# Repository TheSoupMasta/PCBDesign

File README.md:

In the branches section are all the different projects that these PCBs belong to. Check them out!

This branch features some general use PCBs for many different applications.
General Use:
- MUXBreakout v2.sch and MUXBreakout v6.brd. Made for attaching to the RCJ baseplate. May not be in a desirable shape, so be wary. Otherwise, very useful to have around if you run out of analog pins on your PCB.

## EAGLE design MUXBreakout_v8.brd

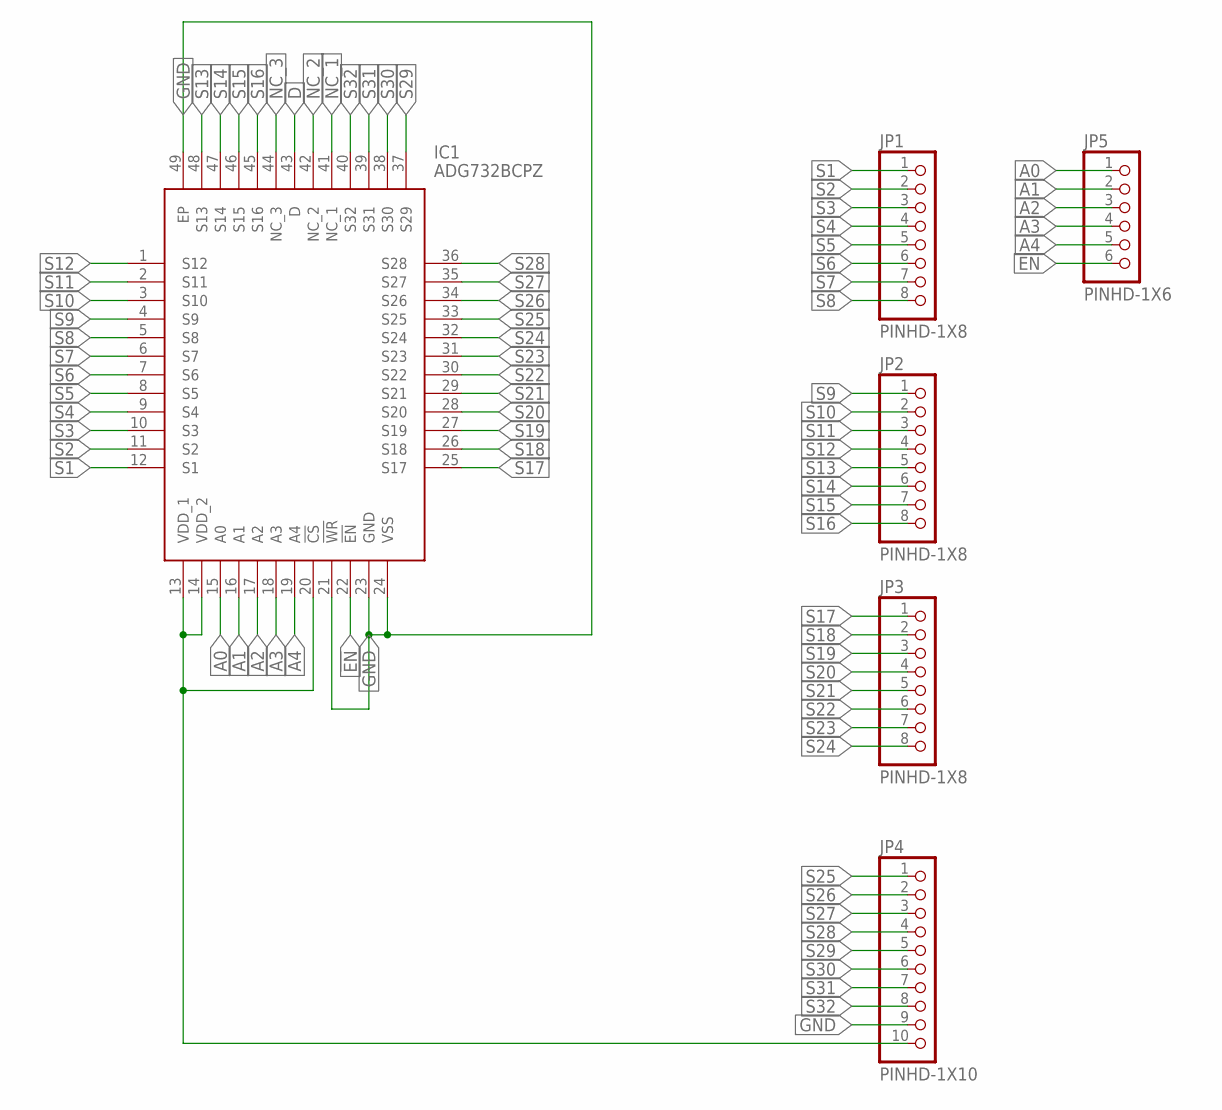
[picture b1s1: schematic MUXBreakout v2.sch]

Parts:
IC1: ADG732BCPZ; QFN50P700X700X100-49N
JP1, JP2, JP3: PINHD-1X8; 1X08
JP4: PINHD-1X10; 1X10
JP5: PINHD-1X6; 1X06

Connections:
!EN: IC1.22 (!EN), JP5.6
A0: IC1.15 (A0), JP5.1
A1: IC1.16 (A1), JP5.2
A2: IC1.17 (A2), JP5.3
A3: IC1.18 (A3), JP5.4
A4: IC1.19 (A4), JP5.5
D: IC1.43 (D)
GND: IC1.21 (!WR), IC1.23 (GND), IC1.24 (VSS), IC1.49 (EP), JP4.9
NC_1: IC1.41 (NC_1)
NC_2: IC1.42 (NC_2)
NC_3: IC1.44 (NC_3)
S1: IC1.12 (S1), JP1.1
S2: IC1.11 (S2), JP1.2
S3: IC1.10 (S3), JP1.3
S4: IC1.9 (S4), JP1.4
S5: IC1.8 (S5), JP1.5
S6: IC1.7 (S6), JP1.6
S7: IC1.6 (S7), JP1.7
S8: IC1.5 (S8), JP1.8
S9: IC1.4 (S9), JP2.1
S10: IC1.3 (S10), JP2.2
S11: IC1.2 (S11), JP2.3
S12: IC1.1 (S12), JP2.4
S13: IC1.48 (S13), JP2.5
S14: IC1.47 (S14), JP2.6
S15: IC1.46 (S15), JP2.7
S16: IC1.45 (S16), JP2.8
S17: IC1.25 (S17), JP3.1
S18: IC1.26 (S18), JP3.2
S19: IC1.27 (S19), JP3.3
S20: IC1.28 (S20), JP3.4
S21: IC1.29 (S21), JP3.5
S22: IC1.30 (S22), JP3.6
S23: IC1.31 (S23), JP3.7
S24: IC1.32 (S24), JP3.8
S25: IC1.33 (S25), JP4.1
S26: IC1.34 (S26), JP4.2
S27: IC1.35 (S27), JP4.3
S28: IC1.36 (S28), JP4.4
S29: IC1.37 (S29), JP4.5
S30: IC1.38 (S30), JP4.6
S31: IC1.39 (S31), JP4.7
S32: IC1.40 (S32), JP4.8
VDD_2: IC1.13 (VDD_1), IC1.14 (VDD_2), IC1.20 (!CS), JP4.10

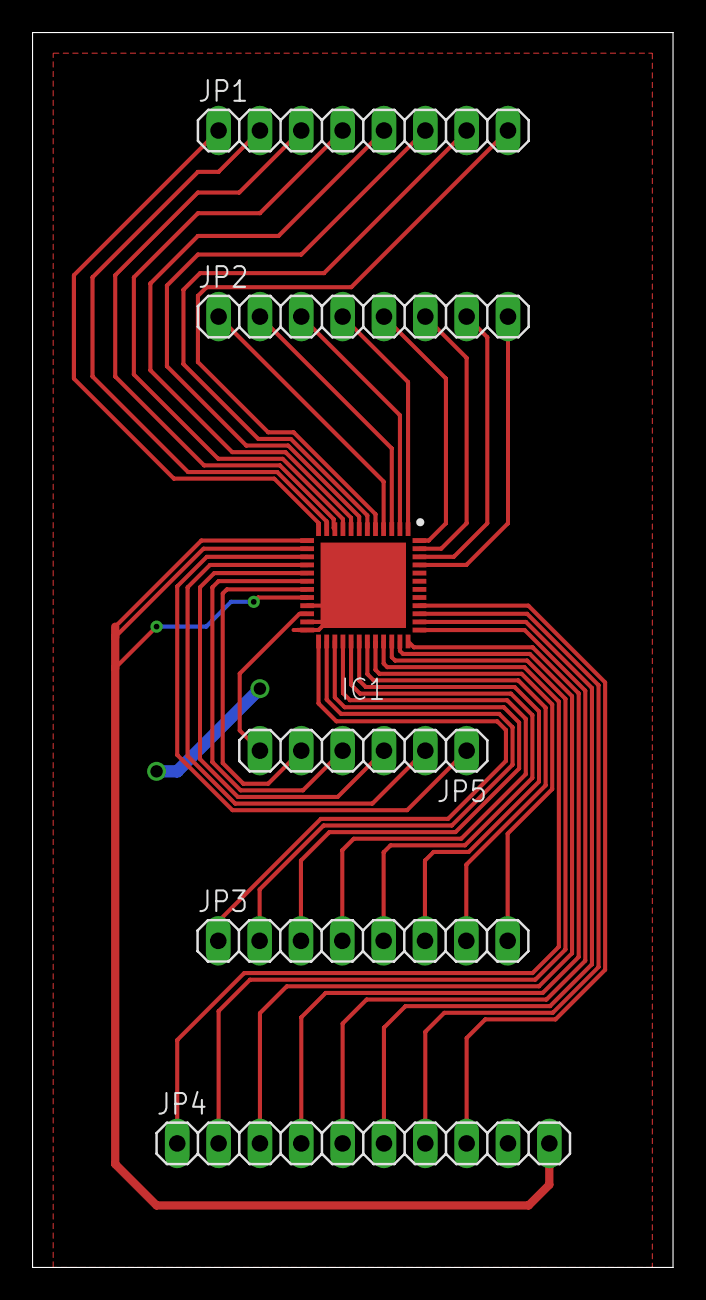
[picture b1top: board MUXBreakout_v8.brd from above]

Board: 2 copper layers, 39.4 x 75.9 mm, 6 parts (0 on the bottom side), 40 nets.

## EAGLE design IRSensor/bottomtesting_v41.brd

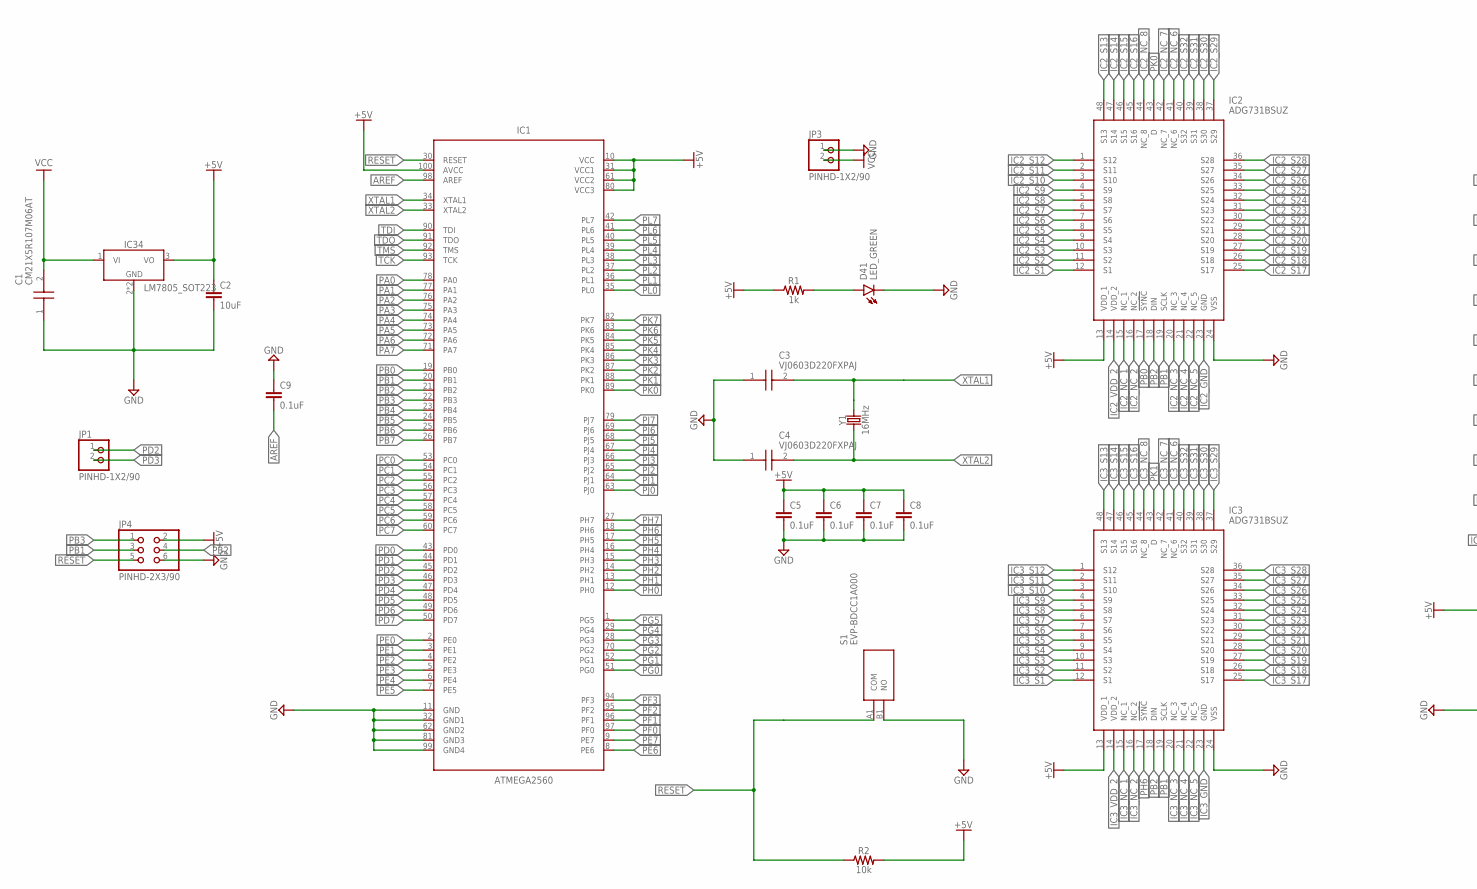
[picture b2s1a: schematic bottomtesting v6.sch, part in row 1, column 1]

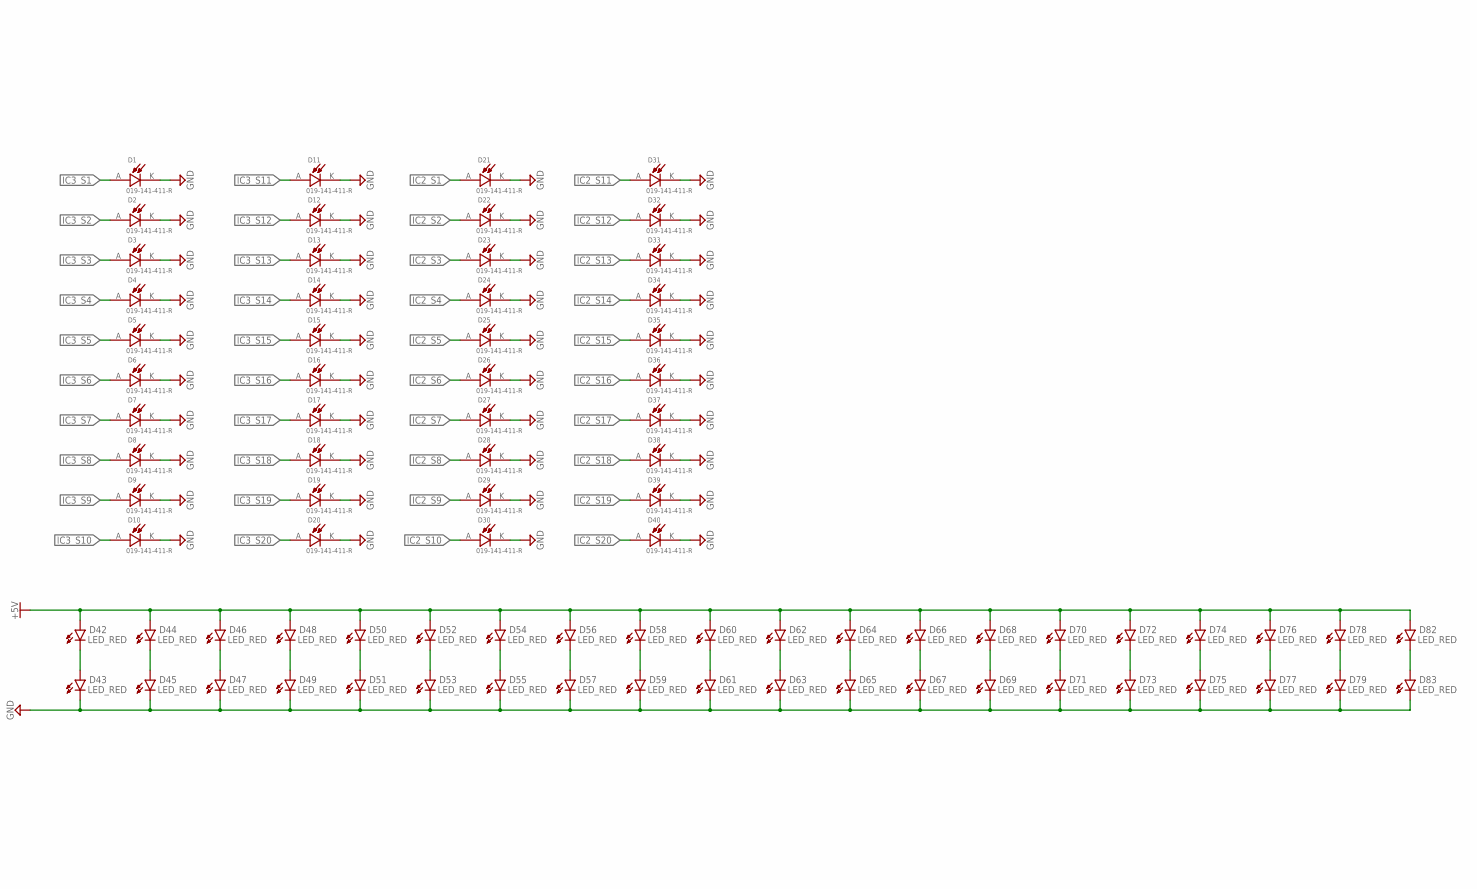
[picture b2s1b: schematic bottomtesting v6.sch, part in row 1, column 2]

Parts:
C1: CM21X5R107M06AT; CAPC2012X135N
C2: 10uF; 0805
C3, C4: VJ0603D220FXPAJ; CAPC1608X94N
C5, C6, C7, C8, C9: 0.1uF; 0402-TIGHT
D1, D2, D3, D4, D5, D6, D7, D8, D9, D10, D11, D12, D13, D14, D15, D16, D17, D18, D19, D20, D21, D22, D23, D24, D25, D26, D27, D28, D29, D30, D31, D32, D33, D34, D35, D36, D37, D38, D39, D40: 019-141-411-R; DIOC2012X80N
D41: LED_GREEN; LEDC1005X25N_FLAT-G
D42, D43, D44, D45, D46, D47, D48, D49, D50, D51, D52, D53, D54, D55, D56, D57, D58, D59, D60, D61, D62, D63, D64, D65, D66, D67, D68, D69, D70, D71, D72, D73, D74, D75, D76, D77, D78, D79, D82, D83: LED_RED; LEDC3216X110N_R
IC1: ATMEGA2560; QFP50P1600X1600X160-100N
IC2, IC3: ADG731BSUZ; QFP50P900X900X120-48N
IC34: LM7805_SOT223; SOT230P700X170-4
JP1, JP3: PINHD-1X2/90; 1X02/90
JP4: PINHD-2X3/90; 2X03/90
R1: 1k; 0603
R2: 10k; 0603
S1: EVP-BDCC1A000; EVPBDCC1A000
Y1: 16MHz; HC49US

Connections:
+5V: C2.1, C5.1, C6.1, C7.1, C8.1, D42.2 (A), D44.2 (A), D46.2 (A), D48.2 (A), D50.2 (A), D52.2 (A), D54.2 (A), D56.2 (A), D58.2 (A), D60.2 (A), D62.2 (A), D64.2 (A), D66.2 (A), D68.2 (A), D70.2 (A), D72.2 (A), D74.2 (A), D76.2 (A), D78.2 (A), D82.2 (A), IC1.10 (VCC), IC1.31 (VCC1), IC1.61 (VCC2), IC1.80 (VCC3), IC1.100 (AVCC), IC2.13 (VDD_1), IC3.13 (VDD_1), IC34.3 (VO), JP4.2, R1.1, R2.2
AREF: C9.2, IC1.98 (AREF)
GND: C1.1, C2.2, C5.2, C6.2, C7.2, C8.2, C9.1, D1.K (C), D2.K (C), D3.K (C), D4.K (C), D5.K (C), D6.K (C), D7.K (C), D8.K (C), D9.K (C), D10.K (C), D11.K (C), D12.K (C), D13.K (C), D14.K (C), D15.K (C), D16.K (C), D17.K (C), D18.K (C), D19.K (C), D20.K (C), D21.K (C), D22.K (C), D23.K (C), D24.K (C), D25.K (C), D26.K (C), D27.K (C), D28.K (C), D29.K (C), D30.K (C), D31.K (C), D32.K (C), D33.K (C), D34.K (C), D35.K (C), D36.K (C), D37.K (C), D38.K (C), D39.K (C), D40.K (C), D41.C, D43.1 (C), D45.1 (C), D47.1 (C), D49.1 (C), D51.1 (C), D53.1 (C), D55.1 (C), D57.1 (C), D59.1 (C), D61.1 (C), D63.1 (C), D65.1 (C), D67.1 (C), D69.1 (C), D71.1 (C), D73.1 (C), D75.1 (C), D77.1 (C), D79.1 (C), D83.1 (C), IC1.11 (GND), IC1.32 (GND1), IC1.62 (GND2), IC1.81 (GND3), IC1.99 (GND4), IC2.24 (VSS), IC3.24 (VSS), IC34.2 (GND), IC34.4 (GND), JP3.1, JP4.6, S1.B1 (NO)
IC2_GND: IC2.23 (GND)
IC2_NC_1: IC2.15 (NC_1)
IC2_NC_2: IC2.16 (NC_2)
IC2_NC_3: IC2.20 (NC_3)
IC2_NC_4: IC2.21 (NC_4)
IC2_NC_5: IC2.22 (NC_5)
IC2_NC_6: IC2.41 (NC_6)
IC2_NC_7: IC2.42 (NC_7)
IC2_NC_8: IC2.44 (NC_8)
IC2_S1: D21.A, IC2.12 (S1)
IC2_S2: D22.A, IC2.11 (S2)
IC2_S3: D23.A, IC2.10 (S3)
IC2_S4: D24.A, IC2.9 (S4)
IC2_S5: D25.A, IC2.8 (S5)
IC2_S6: D26.A, IC2.7 (S6)
IC2_S7: D27.A, IC2.6 (S7)
IC2_S8: D28.A, IC2.5 (S8)
IC2_S9: D29.A, IC2.4 (S9)
IC2_S10: D30.A, IC2.3 (S10)
IC2_S11: D31.A, IC2.2 (S11)
IC2_S12: D32.A, IC2.1 (S12)
IC2_S13: D33.A, IC2.48 (S13)
IC2_S14: D34.A, IC2.47 (S14)
IC2_S15: D35.A, IC2.46 (S15)
IC2_S16: D36.A, IC2.45 (S16)
IC2_S17: D37.A, IC2.25 (S17)
IC2_S18: D38.A, IC2.26 (S18)
IC2_S19: D39.A, IC2.27 (S19)
IC2_S20: D40.A, IC2.28 (S20)
IC2_S21: IC2.29 (S21)
IC2_S22: IC2.30 (S22)
IC2_S23: IC2.31 (S23)
IC2_S24: IC2.32 (S24)
IC2_S25: IC2.33 (S25)
IC2_S26: IC2.34 (S26)
IC2_S27: IC2.35 (S27)
IC2_S28: IC2.36 (S28)
IC2_S29: IC2.37 (S29)
IC2_S30: IC2.38 (S30)
IC2_S31: IC2.39 (S31)
IC2_S32: IC2.40 (S32)
IC2_VDD_2: IC2.14 (VDD_2)
IC3_GND: IC3.23 (GND)
IC3_NC_1: IC3.15 (NC_1)
IC3_NC_2: IC3.16 (NC_2)
IC3_NC_3: IC3.20 (NC_3)
IC3_NC_4: IC3.21 (NC_4)
IC3_NC_5: IC3.22 (NC_5)
IC3_NC_6: IC3.41 (NC_6)
IC3_NC_7: IC3.42 (NC_7)
IC3_NC_8: IC3.44 (NC_8)
IC3_S1: D1.A, IC3.12 (S1)
IC3_S2: D2.A, IC3.11 (S2)
IC3_S3: D3.A, IC3.10 (S3)
IC3_S4: D4.A, IC3.9 (S4)
IC3_S5: D5.A, IC3.8 (S5)
IC3_S6: D6.A, IC3.7 (S6)
IC3_S7: D7.A, IC3.6 (S7)
IC3_S8: D8.A, IC3.5 (S8)
IC3_S9: D9.A, IC3.4 (S9)
IC3_S10: D10.A, IC3.3 (S10)
IC3_S11: D11.A, IC3.2 (S11)
IC3_S12: D12.A, IC3.1 (S12)
IC3_S13: D13.A, IC3.48 (S13)
IC3_S14: D14.A, IC3.47 (S14)
IC3_S15: D15.A, IC3.46 (S15)
IC3_S16: D16.A, IC3.45 (S16)
IC3_S17: D17.A, IC3.25 (S17)
IC3_S18: D18.A, IC3.26 (S18)
IC3_S19: D19.A, IC3.27 (S19)
IC3_S20: D20.A, IC3.28 (S20)
IC3_S21: IC3.29 (S21)
IC3_S22: IC3.30 (S22)
IC3_S23: IC3.31 (S23)
IC3_S24: IC3.32 (S24)
IC3_S25: IC3.33 (S25)
IC3_S26: IC3.34 (S26)
IC3_S27: IC3.35 (S27)
IC3_S28: IC3.36 (S28)
IC3_S29: IC3.37 (S29)
IC3_S30: IC3.38 (S30)
IC3_S31: IC3.39 (S31)
IC3_S32: IC3.40 (S32)
IC3_VDD_2: IC3.14 (VDD_2)
unnamed: D42.1 (C), D43.2 (A)
unnamed: D44.1 (C), D45.2 (A)
unnamed: D46.1 (C), D47.2 (A)
unnamed: D48.1 (C), D49.2 (A)
unnamed: D50.1 (C), D51.2 (A)
unnamed: D52.1 (C), D53.2 (A)
unnamed: D54.1 (C), D55.2 (A)
unnamed: D56.1 (C), D57.2 (A)
unnamed: D58.1 (C), D59.2 (A)
unnamed: D60.1 (C), D61.2 (A)
unnamed: D62.1 (C), D63.2 (A)
unnamed: D41.A, R1.2
unnamed: D64.1 (C), D65.2 (A)
unnamed: D66.1 (C), D67.2 (A)
unnamed: C4.2, Y1.1
unnamed: D68.1 (C), D69.2 (A)
unnamed: D70.1 (C), D71.2 (A)
unnamed: D72.1 (C), D73.2 (A)
unnamed: D74.1 (C), D75.2 (A)
unnamed: D76.1 (C), D77.2 (A)
unnamed: D78.1 (C), D79.2 (A)
unnamed: D82.1 (C), D83.2 (A)
PA0: IC1.78 (PA0)
PA1: IC1.77 (PA1)
PA2: IC1.76 (PA2)
PA3: IC1.75 (PA3)
PA4: IC1.74 (PA4)
PA5: IC1.73 (PA5)
PA6: IC1.72 (PA6)
PA7: IC1.71 (PA7)
PB0: IC1.19 (PB0), IC2.17 (!SYNC)
PB1: IC1.20 (PB1), IC2.19 (SCLK), IC3.19 (SCLK), JP4.3
PB2: IC1.21 (PB2), IC2.18 (DIN), IC3.18 (DIN), JP4.4
PB3: IC1.22 (PB3), JP4.1
PB4: IC1.23 (PB4)
PB5: IC1.24 (PB5)
PB6: IC1.25 (PB6)
PB7: IC1.26 (PB7)
PC0: IC1.53 (PC0)
PC1: IC1.54 (PC1)
PC2: IC1.55 (PC2)
PC3: IC1.56 (PC3)
PC4: IC1.57 (PC4)
PC5: IC1.58 (PC5)
PC6: IC1.59 (PC6)
PC7: IC1.60 (PC7)
PD0: IC1.43 (PD0)
PD1: IC1.44 (PD1)
PD2: IC1.45 (PD2), JP1.1
PD3: IC1.46 (PD3), JP1.2
PD4: IC1.47 (PD4)
PD5: IC1.48 (PD5)
PD6: IC1.49 (PD6)
PD7: IC1.50 (PD7)
PE0: IC1.2 (PE0)
PE1: IC1.3 (PE1)
PE2: IC1.4 (PE2)
PE3: IC1.5 (PE3)
PE4: IC1.6 (PE4)
PE5: IC1.7 (PE5)
PE6: IC1.8 (PE6)
PE7: IC1.9 (PE7)
PF0: IC1.97 (PF0)
PF1: IC1.96 (PF1)
PF2: IC1.95 (PF2)
PF3: IC1.94 (PF3)
PG0: IC1.51 (PG0)
PG1: IC1.52 (PG1)
PG2: IC1.70 (PG2)
PG3: IC1.28 (PG3)
PG4: IC1.29 (PG4)
PG5: IC1.1 (PG5)
PH0: IC1.12 (PH0)
PH1: IC1.13 (PH1)
PH2: IC1.14 (PH2)
PH3: IC1.15 (PH3)
PH4: IC1.16 (PH4)
PH5: IC1.17 (PH5)
PH6: IC1.18 (PH6), IC3.17 (!SYNC)
PH7: IC1.27 (PH7)
PJ0: IC1.63 (PJ0)
PJ1: IC1.64 (PJ1)
PJ2: IC1.65 (PJ2)
PJ3: IC1.66 (PJ3)
PJ4: IC1.67 (PJ4)
PJ5: IC1.68 (PJ5)
PJ6: IC1.69 (PJ6)
PJ7: IC1.79 (PJ7)
PK0: IC1.89 (PK0), IC2.43 (D)
PK1: IC1.88 (PK1), IC3.43 (D)
PK2: IC1.87 (PK2)
PK3: IC1.86 (PK3)
PK4: IC1.85 (PK4)
PK5: IC1.84 (PK5)
PK6: IC1.83 (PK6)
PK7: IC1.82 (PK7)
PL0: IC1.35 (PL0)
PL1: IC1.36 (PL1)
PL2: IC1.37 (PL2)
PL3: IC1.38 (PL3)
PL4: IC1.39 (PL4)
PL5: IC1.40 (PL5)
PL6: IC1.41 (PL6)
PL7: IC1.42 (PL7)
RESET: IC1.30 (RESET), JP4.5, R2.1, S1.A1 (COM)
TCK: IC1.93 (TCK)
TDI: IC1.90 (TDI)
TDO: IC1.91 (TDO)
TMS: IC1.92 (TMS)
VCC: C1.2, IC34.1 (VI), JP3.2
XTAL1: C3.2, IC1.34 (XTAL1), Y1.2
XTAL2: C3.1, C4.1, IC1.33 (XTAL2)

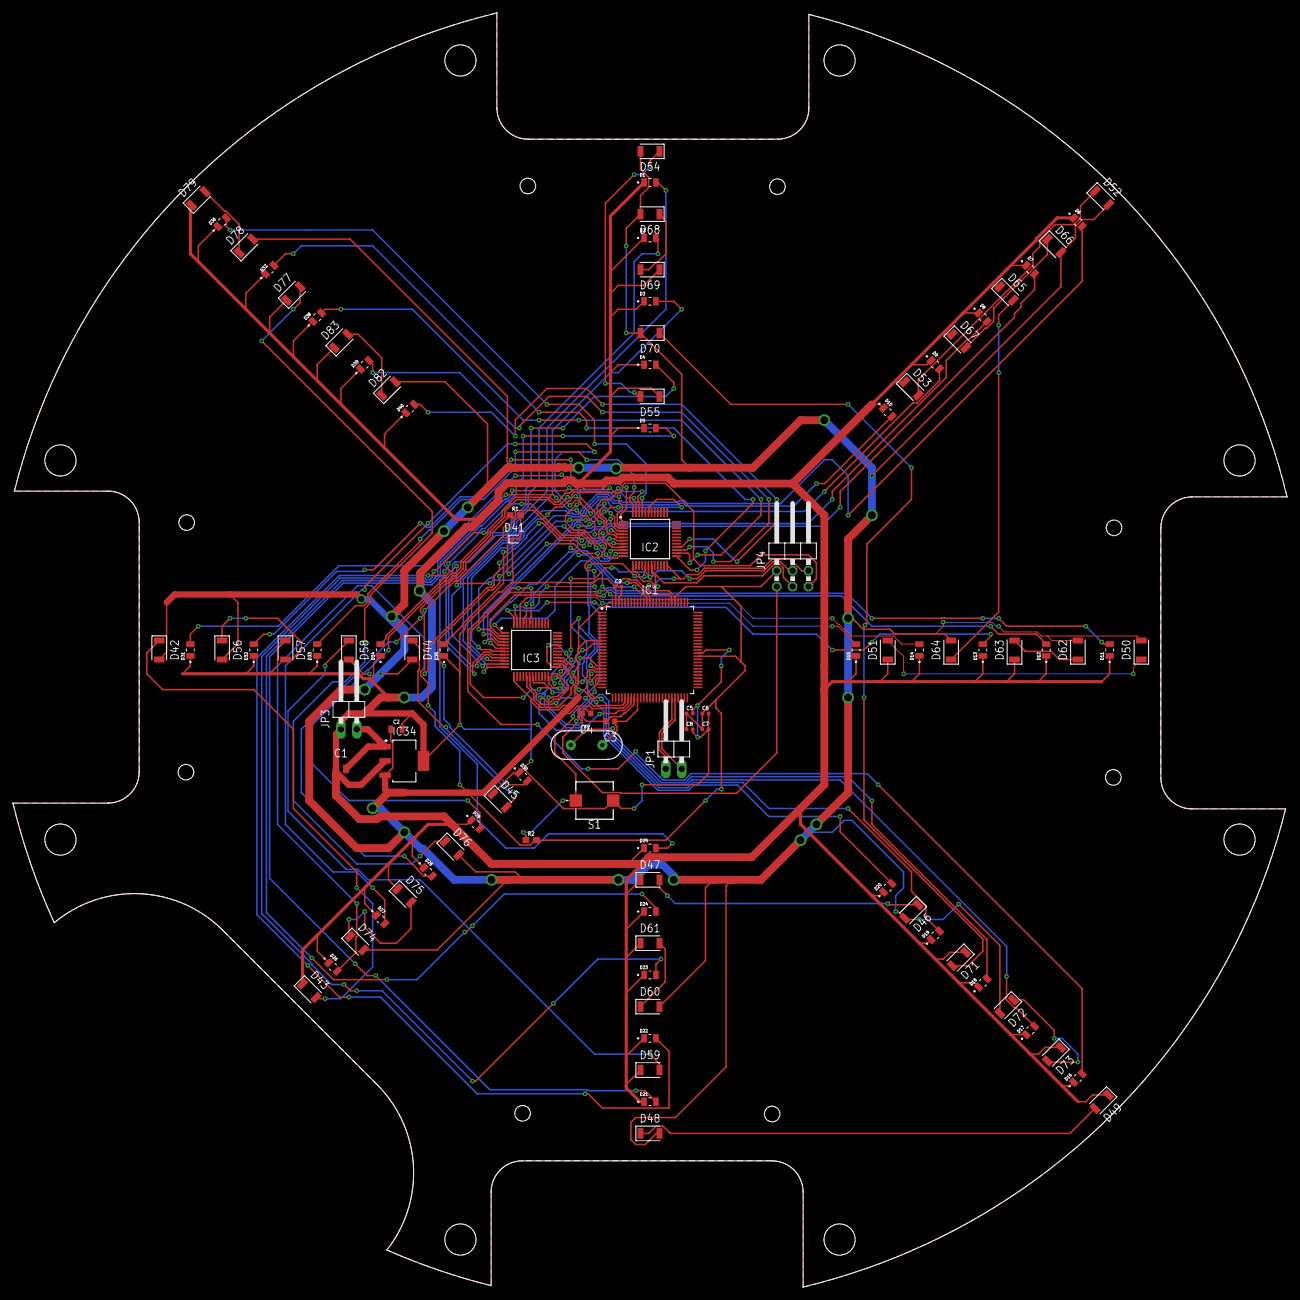
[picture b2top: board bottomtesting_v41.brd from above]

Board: 2 copper layers, 204.2 x 204.2 mm, 101 parts (0 on the bottom side), 78 nets.

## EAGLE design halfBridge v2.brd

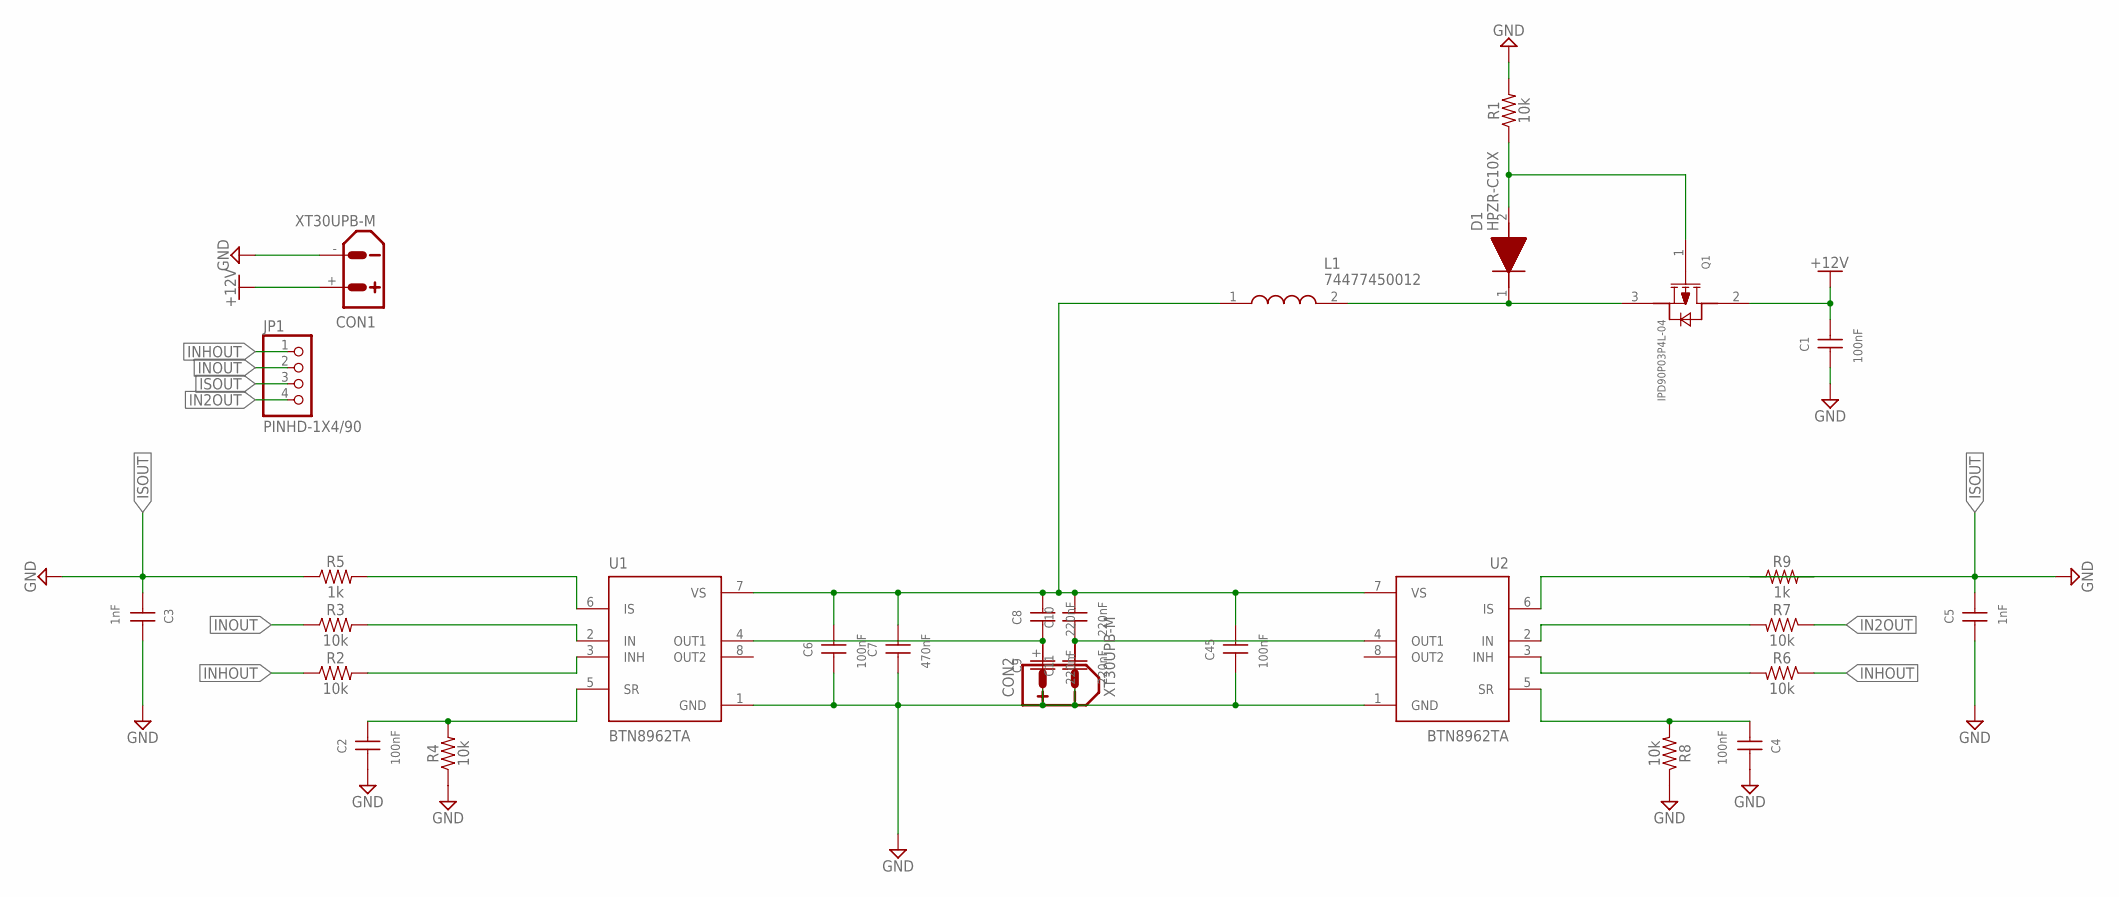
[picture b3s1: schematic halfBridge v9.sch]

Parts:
C1, C2, C4, C6: 100nF; WCAP-CSGP_0603_FI0.35_W
C3, C5: 1nF; WCAP-CSGP_0603_FI0.35_W
C7: 470nF; WCAP-CSGP_0603_FI0.35_W
C8, C9, C10, C11: 220nF; WCAP-CSGP_0603_FI0.35_W
C45: 100nF; WCAP-CSGP_0603_W
CON1, CON2: XT30UPB-M
D1: HPZR-C10X; HPZRC10X
JP1: PINHD-1X4/90; 1X04/90
L1: 74477450012; WE-PD2_5848/582055
Q1: IPD90P03P4L-04; TO228P998X235-3N-2-V
R1, R2, R3, R4, R6, R7, R8: 10k; 0603
R5, R9: 1k; 0603
U1, U2: BTN8962TA; TO127P1500X440-8N-1

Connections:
+12V: C1.2, CON1.+, Q1.2 (DRAIN)
GND: C1.1, C2.1, C3.2, C4.1, C5.2, C6.1, C7.1, C9.1, C11.1, C45.1, CON1.-, R1.2, R4.1, R8.1, U1.1 (GND), U2.1 (GND)
IN2OUT: JP1.4, R7.1
INHOUT: JP1.1, R2.1, R6.1
INOUT: JP1.2, R3.1
ISOUT: C3.1, C5.1, JP1.3, R5.1, R9.1
unnamed: C6.2, C7.2, C8.2, C10.2, C45.2, L1.1, U1.7 (VS), U2.7 (VS)
unnamed: D1.1 (K), L1.2, Q1.3 (SOURCE)
unnamed: D1.2 (A), Q1.1 (GATE), R1.1
unnamed: R2.2, U1.3 (INH)
unnamed: R3.2, U1.2 (IN)
unnamed: C2.2, R4.2, U1.5 (SR)
unnamed: R5.2, U1.6 (IS)
unnamed: R6.2, U2.3 (INH)
unnamed: R7.2, U2.2 (IN)
unnamed: C4.2, R8.2, U2.5 (SR)
unnamed: R9.2, U2.6 (IS)
unnamed: C8.1, C9.2, CON2.+, U1.4 (OUT1)
unnamed: C10.1, C11.2, CON2.-, U2.4 (OUT1)

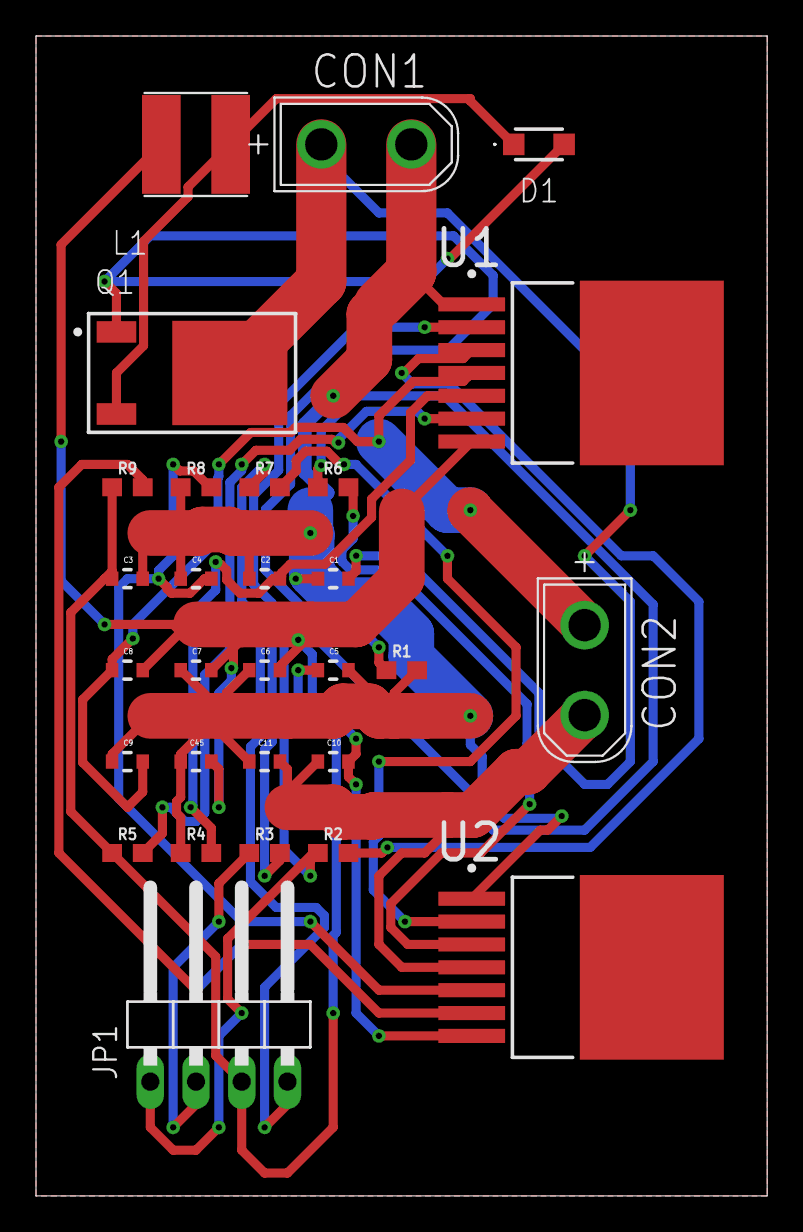
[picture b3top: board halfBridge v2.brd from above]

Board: 2 copper layers, 40.6 x 64.4 mm, 29 parts (0 on the bottom side), 19 nets.

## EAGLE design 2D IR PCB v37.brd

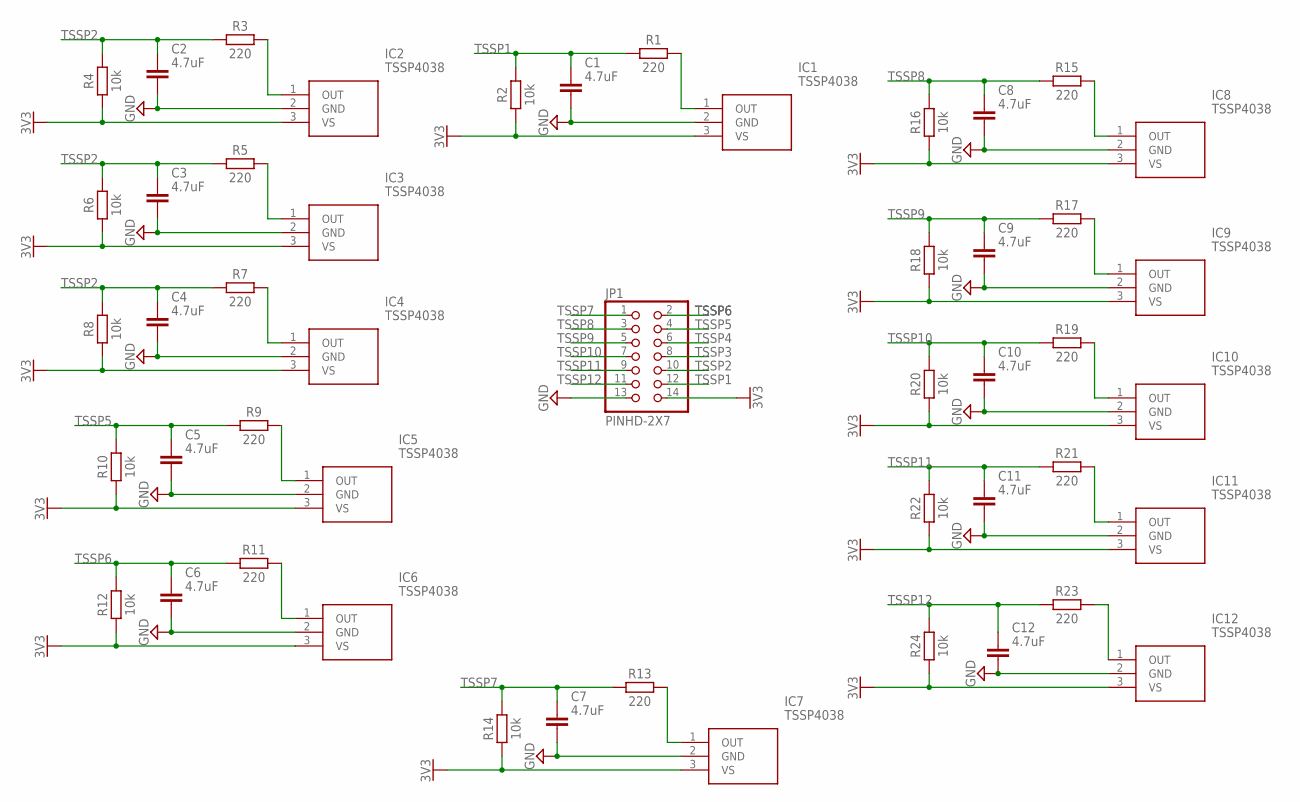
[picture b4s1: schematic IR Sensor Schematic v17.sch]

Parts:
C1, C2, C3, C4, C5, C6, C7, C8, C9, C10, C11, C12: 4.7uF; CAPC3216X135
IC1, IC2, IC3, IC4, IC5, IC6, IC7, IC8, IC9, IC10, IC11, IC12: TSSP4038
JP1: PINHD-2X7; 2X07
R1, R3, R5, R7, R9, R11, R13, R15, R17, R19, R21, R23: 220; RESC3216X70
R2, R4, R6, R8, R10, R12, R14, R16, R18, R20, R22, R24: 10k; RESC3216X70

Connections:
3V3: IC1.3 (VS), IC2.3 (VS), IC3.3 (VS), IC4.3 (VS), IC5.3 (VS), IC6.3 (VS), IC7.3 (VS), IC8.3 (VS), IC9.3 (VS), IC10.3 (VS), IC11.3 (VS), IC12.3 (VS), JP1.14, R2.1, R4.1, R6.1, R8.1, R10.1, R12.1, R14.1, R16.1, R18.1, R20.1, R22.1, R24.1
GND: C1.2, C2.2, C3.2, C4.2, C5.2, C6.2, C7.2, C8.2, C9.2, C10.2, C11.2, C12.2, IC1.2 (GND), IC2.2 (GND), IC3.2 (GND), IC4.2 (GND), IC5.2 (GND), IC6.2 (GND), IC7.2 (GND), IC8.2 (GND), IC9.2 (GND), IC10.2 (GND), IC11.2 (GND), IC12.2 (GND), JP1.13
unnamed: IC12.1 (OUT), R23.2
unnamed: IC1.1 (OUT), R1.2
unnamed: IC2.1 (OUT), R3.2
unnamed: IC3.1 (OUT), R5.2
unnamed: IC4.1 (OUT), R7.2
unnamed: IC5.1 (OUT), R9.2
unnamed: IC6.1 (OUT), R11.2
unnamed: IC7.1 (OUT), R13.2
unnamed: IC8.1 (OUT), R15.2
unnamed: IC9.1 (OUT), R17.2
unnamed: IC10.1 (OUT), R19.2
unnamed: IC11.1 (OUT), R21.2
TSSP1: C1.1, JP1.12, R1.1, R2.2
TSSP2: C2.1, C3.1, C4.1, JP1.10, R3.1, R4.2, R5.1, R6.2, R7.1, R8.2
TSSP3: JP1.8
TSSP4: JP1.6
TSSP5: C5.1, JP1.4, R9.1, R10.2
TSSP6: C6.1, JP1.2, R11.1, R12.2
TSSP7: C7.1, JP1.1, R13.1, R14.2
TSSP8: C8.1, JP1.3, R15.1, R16.2
TSSP9: C9.1, JP1.5, R17.1, R18.2
TSSP10: C10.1, JP1.7, R19.1, R20.2
TSSP11: C11.1, JP1.9, R21.1, R22.2
TSSP12: C12.1, JP1.11, R23.1, R24.2

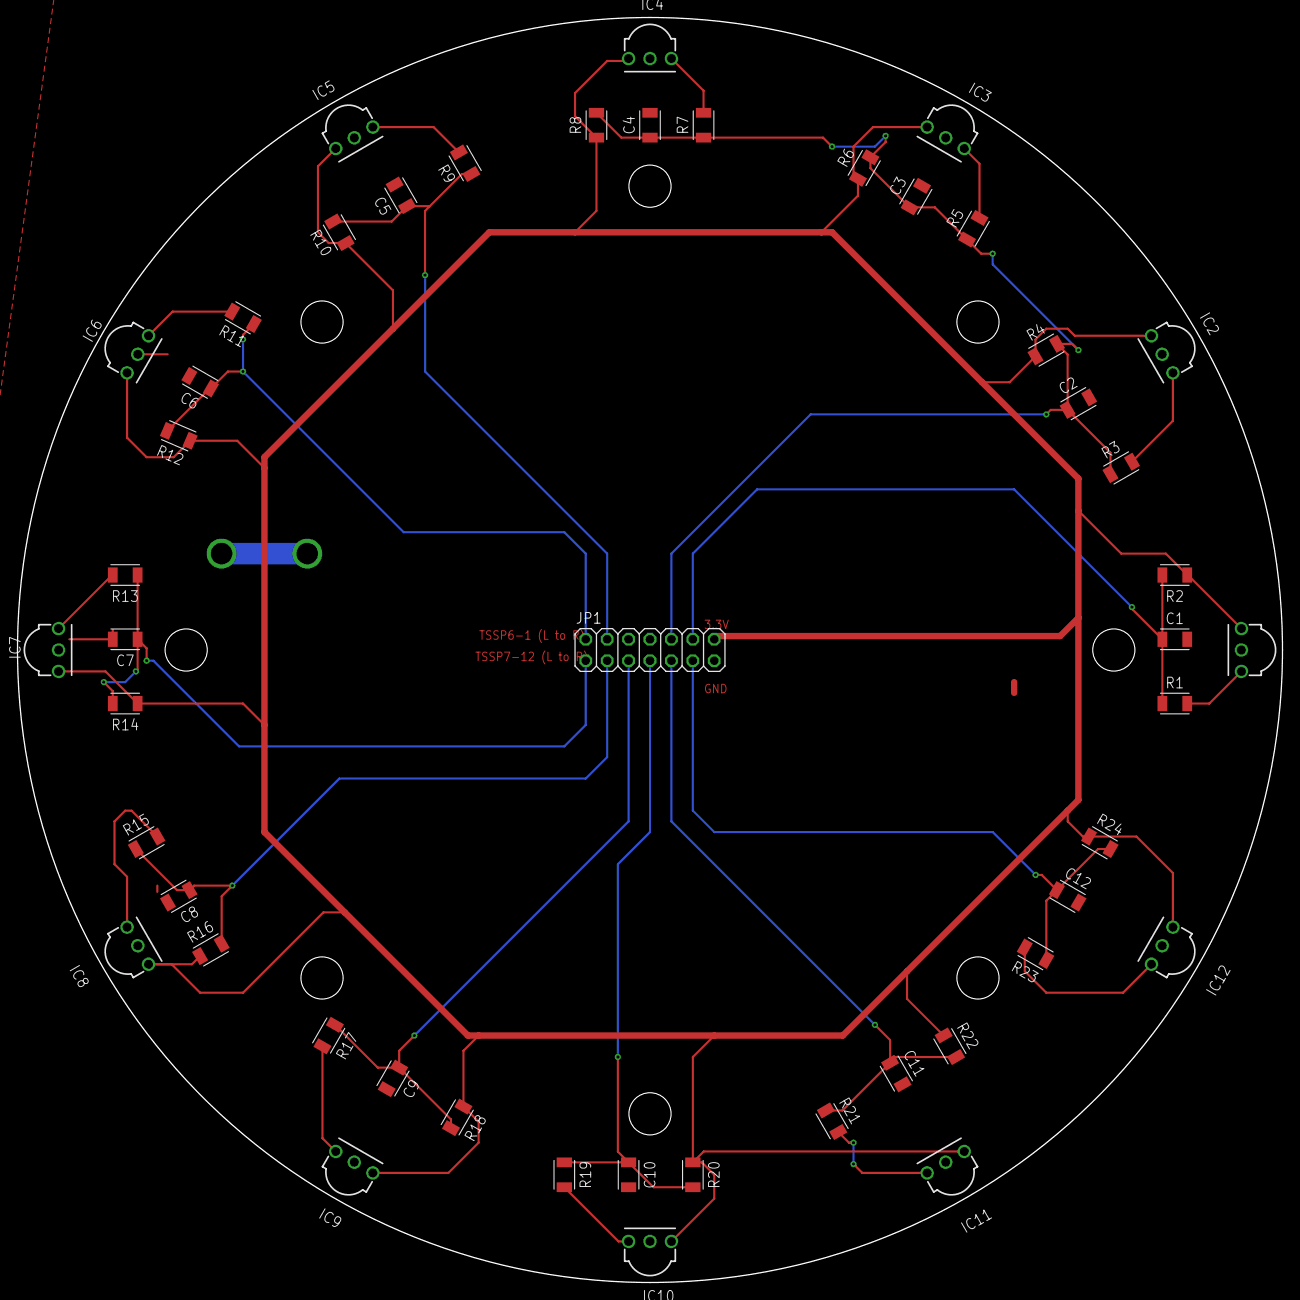
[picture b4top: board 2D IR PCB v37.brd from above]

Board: 2 copper layers, 150.0 x 150.0 mm, 49 parts (0 on the bottom side), 24 nets.

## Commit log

2024-03-02 added files
2024-03-02 fixed files

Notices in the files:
parts and their libraries:
SparkFun-Resistors: Licensing: Creative Commons ShareAlike 4.0 International - https://creativecommons.org/licenses/by-sa/4.0
Wurth_Capacitors_WCAP-CSGP: Copyright: Würth Elektronik
